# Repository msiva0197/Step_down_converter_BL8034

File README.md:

# BL8034 Step-Down (Buck) Converter: 15V to 5V @ 2A

## Overview

TASK: https://docs.google.com/document/d/1YuXwvlgvRe4ZNiqs0p8PUdCa3dj_ZyPA0Ex9oUbwFSo/edit?usp=sharing

This repository contains an open-source, compact 2-layer PCB design for a DC-DC step-down converter using the **BL8034** synchronous buck regulator. This specific design is optimized to step down a **15V input to a stable 5V output**, supporting a continuous load current of **2A**. 

The design addresses critical power routing and thermal management requirements, ensuring stable operation without overheating or saturating the components.

## Key Specifications

* **Input Voltage (Vin):** 15V Nominal 
* **Output Voltage (Vout):** 5V
* **Continuous Output Current:** 2A
* **Switching Frequency:** High frequency (internal)
* **PCB Layers:** 2 Layers (Top/Bottom)
* **Dimensions:** 38 mm x 29 mm

## PCB Layout Highlights

To ensure safe and reliable 2A continuous operation, this layout incorporates several best practices:

* **1mm Power Polygons:** The critical high-current paths (`V_IN+`, `SW` node, and `V_OUT_5V`) utilize wide 1mm copper polygons instead of thin traces. This minimizes impedance, voltage drop, and localized heating.
* **Optimized Ground Loop:** The ground pad of the input capacitor (C1) is routed directly to the IC's exposed thermal pad (Pin 9) via a solid top-layer copper pour, drastically reducing high-frequency EMI.
* **Proper Component Sizing:** Avoiding standard 0603 packages for high-power paths. The inductor uses an NR5040 footprint to handle high saturation currents, and the main capacitors use 1206 packages to mitigate DC-bias capacitance loss at 15V.
* **Thermal Management:** Extensive thermal vias are placed under the BL8034 IC's exposed center pad to dissipate heat effectively into the bottom ground plane.

## Bill of Materials (BOM)

| Reference | Qty | Value | Footprint | Part Type / Description |
| :--- | :--- | :--- | :--- | :--- |
| **U1** | 1 | BL8034 | ESOP-8 | Synchronous Step-Down Converter IC |
| **L2** | 1 | 4.7µH | NR5040 | SMD Power Inductor (NR5040T4R7N, Isat > 3A) |
| **C1, C3** | 2 | 22µF | 1206 | Ceramic Capacitor (Minimum 25V rating for C1) |
| **C2** | 1 | 1µF | 0603 | Ceramic Boot Capacitor |
| **R2** | 1 | 2.2KΩ | 0603 | SMD Resistor (Feedback bottom) |
| **R3** | 1 | 10KΩ | 0603 | SMD Resistor (Feedback top) |
| **R4** | 1 | 100KΩ | 0603 | SMD Resistor (Enable Pull-up) |
| **TP1 - TP4**| 4 | - | 5.0x8.0mm | Terminal Pads for VIN+, VIN-, VOUT+, VOUT- |

*Note: Output voltage is set by the feedback resistor divider R3 and R2. $V_{OUT} = 0.923V \times (1 + 10k/2.2k) =5.118 volt$*

## Manufacturing Details

* **Gerber Files:** Available in the `releases` section or the `gerber/` folder.
* **Silkscreen Note:** The board features clear terminal labels (`V_IN+`, `V_IN-`, `V_OUT+`, `V_OUT-`) and mounting holes for easy enclosure integration.

## Disclaimer

This is an open-source hardware project provided "as-is". Please verify all component ratings (especially capacitor voltage ratings and inductor saturation currents) before assembly.

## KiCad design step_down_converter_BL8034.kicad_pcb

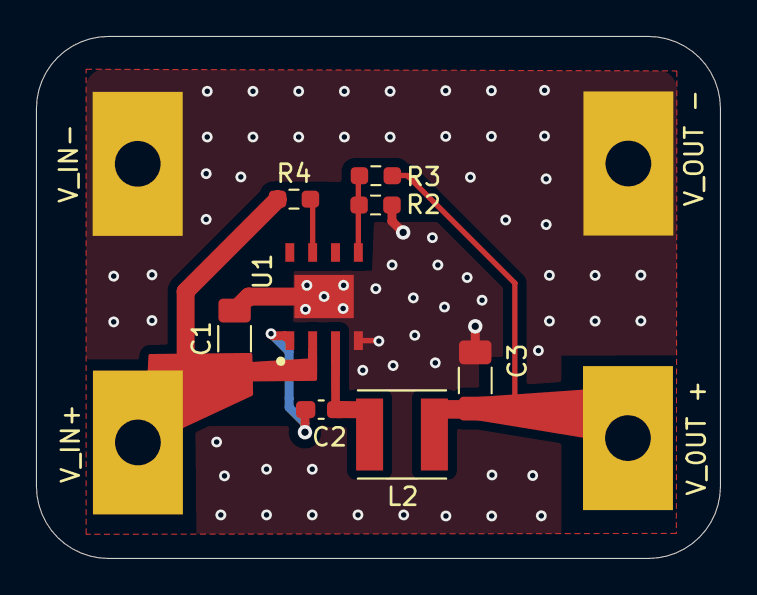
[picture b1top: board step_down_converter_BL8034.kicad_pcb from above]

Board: 2 copper layers, 38.0 x 29.0 mm, 12 parts (0 on the bottom side), 7 nets.

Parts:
C1, C3: 22uF; C_1206_3216Metric_Pad1.33x1.80mm_HandSolder
C2: 1uF; C_0603_1608Metric_Pad1.08x0.95mm_HandSolder
L2: NR5040T4R7N; IND_NR5040T330M
R2: 2.2K; R_0603_1608Metric_Pad0.98x0.95mm_HandSolder
R3: 10K; R_0603_1608Metric_Pad0.98x0.95mm_HandSolder
R4: 100K; R_0603_1608Metric_Pad0.98x0.95mm_HandSolder
U1: BL8034; ESOP8_5.0x6.0mm_P1.27mm_EP2.4x3.3mm
V_0UT +: power pad; TestPoint_THTPad_4.0x4.0mm_Drill2.0mm
V_IN+: power pad; TestPoint_THTPad_4.0x4.0mm_Drill2.0mm
V_IN-: power pad; TestPoint_THTPad_4.0x4.0mm_Drill2.0mm
V_OUT -: power pad; TestPoint_THTPad_4.0x4.0mm_Drill2.0mm

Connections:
EN: R4.2, U1.7 (EN)
FB: R2.1, R3.2, U1.5 (FB)
GND: C1.2, C3.2, R2.2, U1.4 (GND), U1.9 (PAD), V_IN-.1, V_OUT -.1
unnamed: C2.1, U1.1 (BST)
SW: C2.2, L2.1, U1.3 (SW)
VIN: C1.1, R4.1, U1.2 (VIN), V_IN+.1
VOUT_5V: C3.1, L2.2, R3.1, V_0UT +.1

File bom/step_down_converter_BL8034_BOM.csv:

"Reference","Qty","Value","DNP","Exclude from BOM","Exclude from Board","Footprint","Datasheet"
"C1,C3","2","22uF","","","","Capacitor_SMD:C_1206_3216Metric_Pad1.33x1.80mm_HandSolder","~"
"C2","1","1uF","","","","Capacitor_SMD:C_0603_1608Metric_Pad1.08x0.95mm_HandSolder","~"
"L2","1","NR5040T4R7N","","","","NR5040T330M:IND_NR5040T330M",""
"R2","1","2.2K","","","","Resistor_SMD:R_0603_1608Metric_Pad0.98x0.95mm_HandSolder","~"
"R3","1","10K","","","","Resistor_SMD:R_0603_1608Metric_Pad0.98x0.95mm_HandSolder","~"
"R4","1","100K","","","","Resistor_SMD:R_0603_1608Metric_Pad0.98x0.95mm_HandSolder","~"
"TP1,TP2,TP3,TP4","4","power pad","","","","TestPoint:TestPoint_THTPad_4.0x4.0mm_Drill2.0mm","~"
"U1","1","BL8034","","","","BL8034:ESOP8_5.0x6.0mm_P1.27mm_EP2.4x3.3mm","BL8034_Datasheet_V1_3.pdf"
